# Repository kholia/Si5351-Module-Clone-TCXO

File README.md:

#### Notes

Note: We are using KiCad 7.0.x version to build this project.

[UPDATE] The design was validated on 27th-Feb-2023. It works really well for
WSPR @ 28 MHz where the original Adafruit Si5351 module is barely usable.

#### JLC PCBA files

- [Gerbers](./Adafruit-Si5351A-v3/jlcpcb/production_files/GERBER-Adafruit-Si5351A.zip)
- [BOM](./Adafruit-Si5351A-v3/jlcpcb/production_files/BOM-Adafruit-Si5351A.csv)
- [CPL](./Adafruit-Si5351A-v3/jlcpcb/production_files/CPL-Adafruit-Si5351A.csv)

#### PCB render

#### BOM Sources

- https://www.lcsc.com/ - MS5351M

- https://www.comkey.in/ - SMD passives

- https://www.ktron.in/ - SMA connectors for cheap

- https://www.semikart.com/ - TCXOs

Note: International buyers can buy from DigiKey or Mouser.

#### Credits

- Sambhu Dharmadevan (VU3KQF)

- Dhiru Kholia (VU3CER)

#### Supported TCXO Modules

- [DEFAULT] KDS Daishinku 1XTW26000MAA (26 MHz)

- YXC Crystal Oscillators OW2EL89CENUXK7YLC-25M

- huaxindianzi 3T025000VX - 25 MHz

- Jauch Quartz O 25,0-JT32C-A-K-3,3-LF

- Abracon ASTX-H11-25.000MHZ-T

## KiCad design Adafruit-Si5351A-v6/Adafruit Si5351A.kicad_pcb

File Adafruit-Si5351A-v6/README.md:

This version is ready for JLCPCB's PCBA process. Enjoy! ;)

This project uses KiCad 9.0.

Update (Feb-2026): These `Adafruit-Si5351A-v6` PCBs were assembled by JLCPCB and they work great!

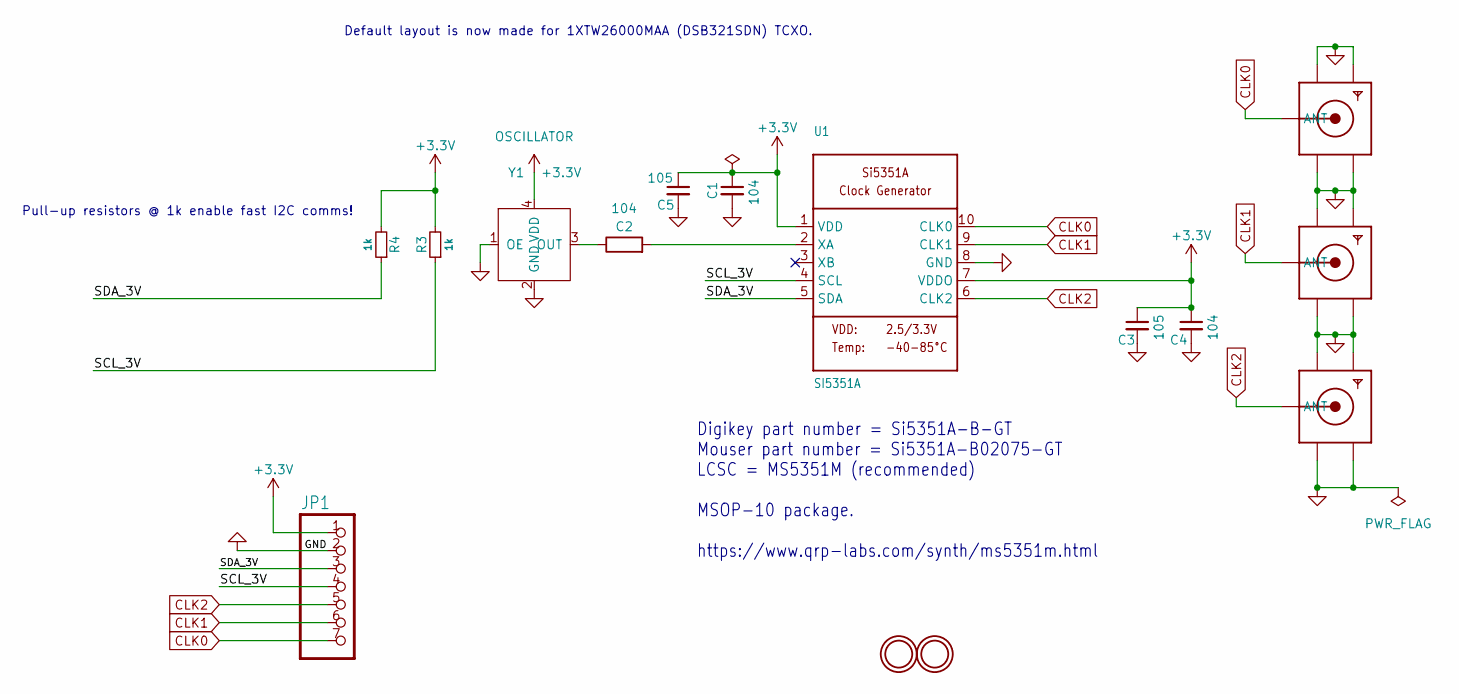
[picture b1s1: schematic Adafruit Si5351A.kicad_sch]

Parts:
C1, C2, C4: 104; C_0603_1608Metric
C3, C5: 105; C_0603_1608Metric
H1, H2: MOUNTINGHOLE2.5; MountingHole_2.5mm
JP1: 1X07_ROUND_76
R3, R4: 1k; R_0805_2012Metric_Pad1.20x1.40mm_HandSolder
U1: SI5351A; MSOP-10_3x3mm_P0.5mm
X1, X2, X3: SMA_EDGELAUNCH
Y1: OSCILLATOR; OSC-SMD_4P-L3.2-W2.5-BL_1XTV

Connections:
+3.3V: C1.1, C3.1, C4.1, C5.1, JP1.1, R3.2, R4.2, U1.1 (VDD), U1.7 (VDDO), Y1.4 (VDD)
/SCL_3V: JP1.4, R3.1, U1.4 (SCL)
/SDA_3V: JP1.3, R4.1, U1.5 (SDA)
CLK0: JP1.7, U1.10 (CLK0), X1.P (ANT)
CLK1: JP1.6, U1.9 (CLK1), X2.P (ANT)
CLK2: JP1.5, U1.6 (CLK2), X3.P (ANT)
GND: C1.2, C3.2, C4.2, C5.2, JP1.2, U1.8 (GND), X1.GND@1 (GND4), X1.GND@2 (GND3), X1.GND@3 (GND2), X1.GND@4 (GND1), X2.GND@1 (GND4), X2.GND@2 (GND3), X2.GND@3 (GND2), X2.GND@4 (GND1), X3.GND@1 (GND4), X3.GND@2 (GND3), X3.GND@3 (GND2), X3.GND@4 (GND1), Y1.1 (OE), Y1.2 (GND)
unnamed: C2.2, U1.2 (XA)
unnamed: C2.1, Y1.3 (OUT)

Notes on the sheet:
Default layout is now made for 1XTW26000MAA (DSB321SDN) TCXO.
Pull-up resistors @ 1k enable fast I2C comms!
Digikey part number = Si5351A-B-GT Mouser part number = Si5351A-B02075-GT LCSC = MS5351M (recommended) MSOP-10 package. https://www.qrp-labs.com/synth/ms5351m.html

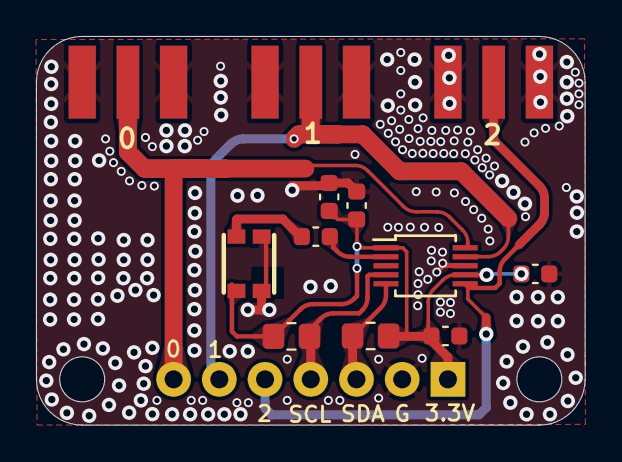
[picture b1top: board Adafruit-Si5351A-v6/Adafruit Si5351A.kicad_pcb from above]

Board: 2 copper layers, 30.5 x 21.6 mm, 15 parts (0 on the bottom side), 9 nets.

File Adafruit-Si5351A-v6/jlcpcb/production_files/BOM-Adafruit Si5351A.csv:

Comment,Designator,Footprint,LCSC,Quantity
104,"C1,C2,C4",C_0603_1608Metric,C14663,3
105,"C3,C5",C_0603_1608Metric,C15849,2
1k,"R3,R4",R_0805_2012Metric_Pad1.20x1.40mm_HandSolder,C17513,2
OSCILLATOR,Y1,OSC-SMD_4P-L3.2-W2.5-BL_1XTV,C48888230,1
SI5351A,U1,MSOP-10_3x3mm_P0.5mm,C1509083,1

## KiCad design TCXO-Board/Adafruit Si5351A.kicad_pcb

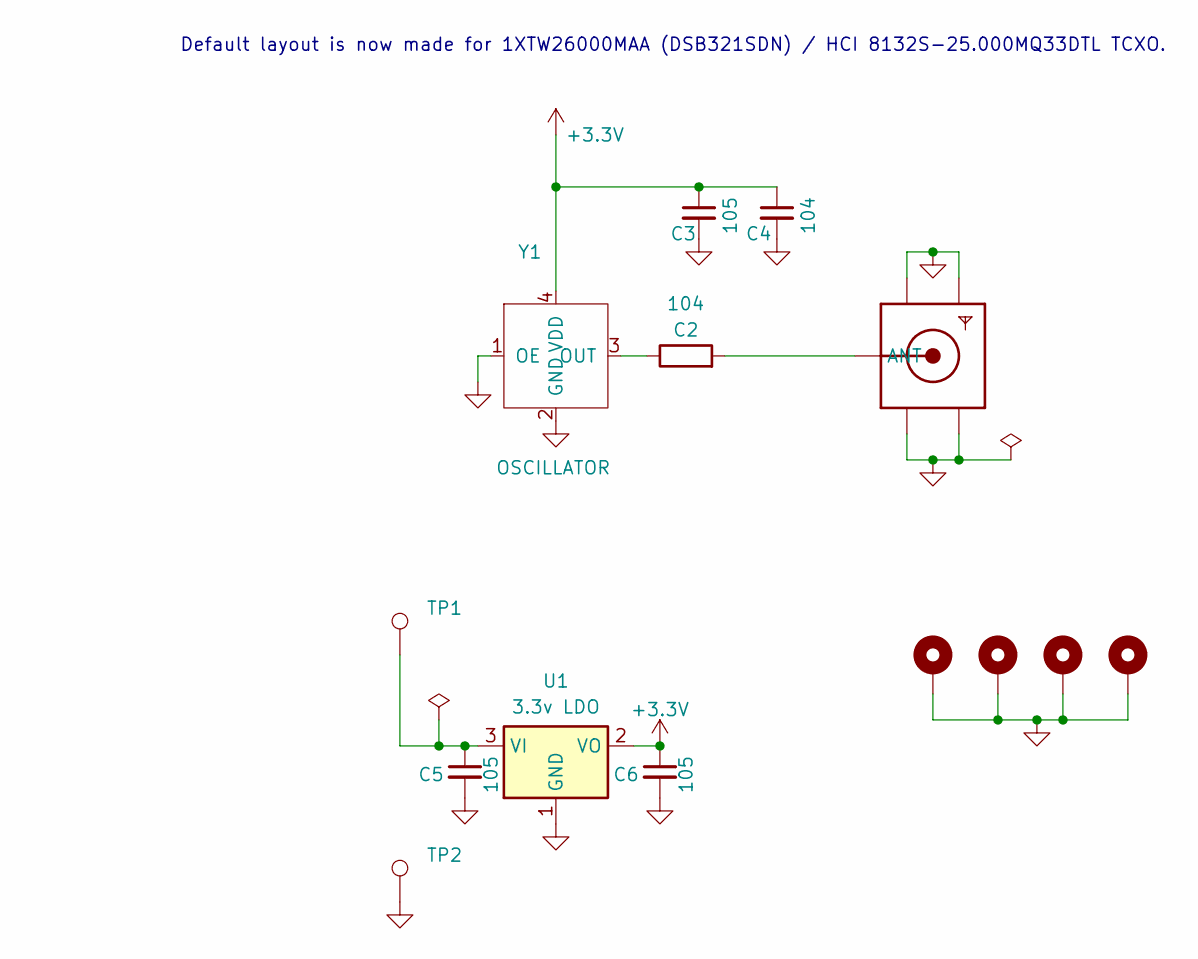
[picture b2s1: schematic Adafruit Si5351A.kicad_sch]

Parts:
C2, C4: 104; C_1206_3216Metric_Pad1.33x1.80mm_HandSolder
C3, C5, C6: 105; C_1206_3216Metric_Pad1.33x1.80mm_HandSolder
H1, H2, H3, H4: MountingHole_M3_3.2mm_Pad; MountingHole_3.2mm_M3_Pad_Via
TP1, TP2: TestPoint; TestPoint_THTPad_4.0x4.0mm_Drill2.0mm
U1: 3.3v LDO; SOT-223-3_TabPin2
X1: SMA_EDGELAUNCH_Same
Y1: OSCILLATOR; Crystal_SMD_3225-4Pin_3.2x2.5mm_HandSoldering

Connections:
+3.3V: C3.1, C4.1, C6.1, U1.2 (VO), Y1.4 (VDD)
GND: C3.2, C4.2, C5.2, C6.2, H1.1, H2.1, H3.1, H4.1, TP2.1, U1.1 (GND), X1.GND@1 (GND4), X1.GND@2 (GND3), X1.GND@3 (GND2), X1.GND@4 (GND1), Y1.1 (OE), Y1.2 (GND)
unnamed: C5.1, TP1.1, U1.3 (VI)
unnamed: C2.2, X1.P (ANT)
unnamed: C2.1, Y1.3 (OUT)

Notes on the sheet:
Default layout is now made for 1XTW26000MAA (DSB321SDN) / HCI 8132S-25.000MQ33DTL TCXO.

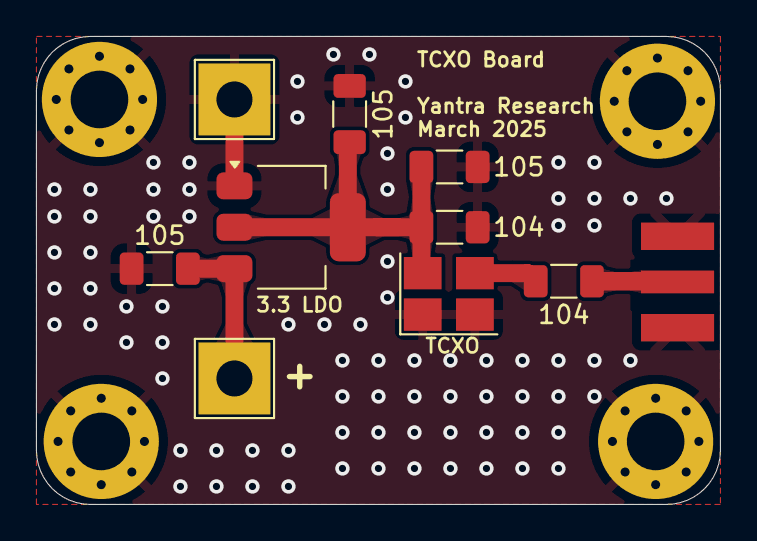
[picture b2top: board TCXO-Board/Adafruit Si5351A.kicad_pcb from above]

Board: 2 copper layers, 38.0 x 26.0 mm, 14 parts (0 on the bottom side), 5 nets.

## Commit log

2016-08-04 init
2023-01-12 Native TCXO support
    Also add experimental support for 'KDS Daishinku 1XTW26000MAA' TCXO.
2023-12-05 KDS Daishinku 1XTW26000MAA TCXO is default now
2025-04-17 More compliant product
2025-07-23 Make 'Si5351-Trimmed-Module*' public
2026-02-21 Adafruit-Si5351A-v6
